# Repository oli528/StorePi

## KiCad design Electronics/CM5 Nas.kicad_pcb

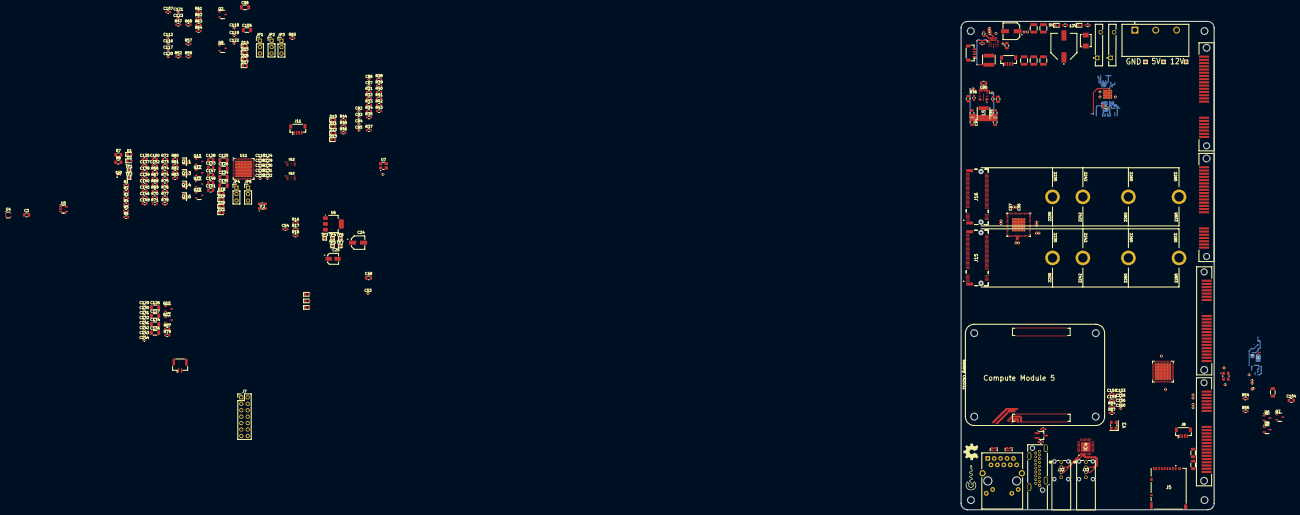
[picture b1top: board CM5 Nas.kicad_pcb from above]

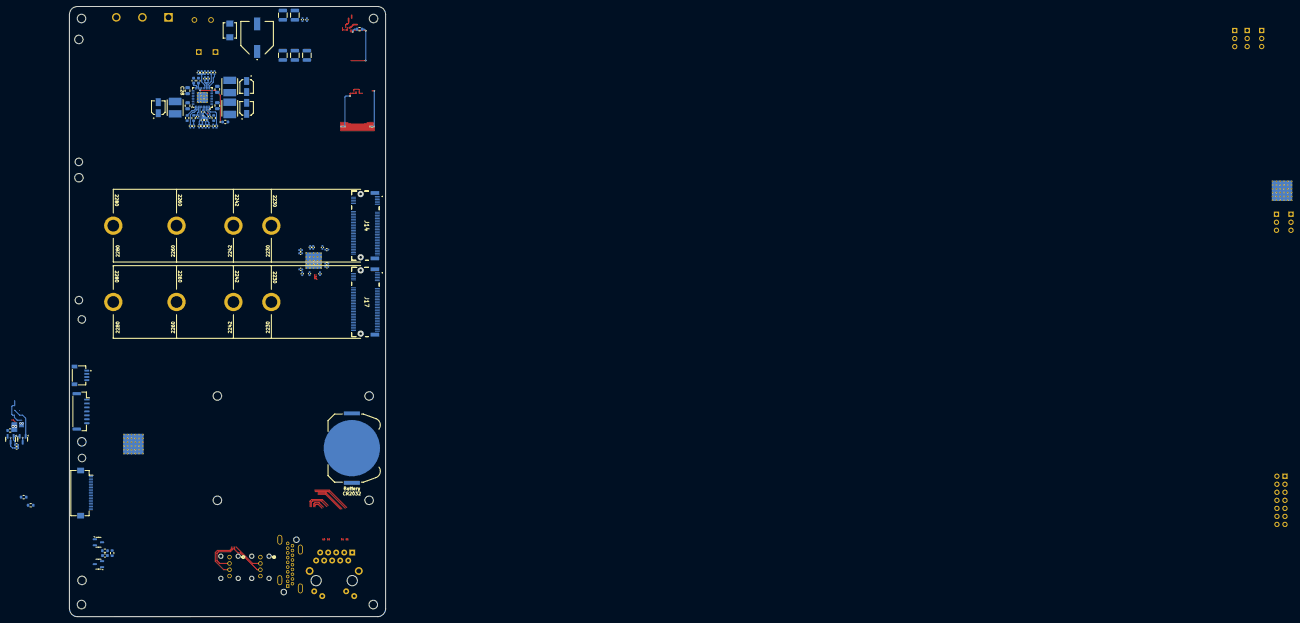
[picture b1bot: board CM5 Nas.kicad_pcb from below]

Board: 4 copper layers, 100.0 x 193.0 mm, 370 parts (78 on the bottom side), 312 nets.

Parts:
+5V1, +12V1: TestPoint; TestPoint_Pad_1.0x1.0mm
BT1: Battery_Cell; BatteryHolder_Keystone_3034_1x20mm
C1, C2, C42, C54, C137, C138, C139, C140, C145, C146, C149, C150, C152, C154, C159: 100n; C_0603_1608Metric
C3, C77, C81: 10u; C_0805_2012Metric
C4, C12: 1u; C_1210_3225Metric
C5, C13: 1000u; EEE0JA152UAP
C6, C7, C8, C9, C14, C15, C16, C17: 10u; C_1210_3225Metric
C10, C11, C18, C19, C44, C56, C57, C58, C59, C60, C61, C62, C63, C64, C65, C66, C67, C68, C69, C70, C71, C72, C73, C74, C75, C76, C79, C82, C83, C84, C85, C86, C87, C88, C89, C109, C110, C111, C112, C116, C117, C120, C121, C123#2: 100n; C_0402_1005Metric
C20, C21, C27, C28: 22u; C_0805_2012Metric
C22, C50, C51: 100p; C_0402_1005Metric
C23: 10u; C_0603_1608Metric
C24: 10u; CAP_EEEFK1H100UR
C25, C32, C34, C37: 22u; CAP_EEEFK1A220AR
C26, C30, C31, C38, C39, C40, C41, C46, C47: 4n7; C_0402_1005Metric
C29: 3u3; C_0603_1608Metric
C33, C35, C36: 47n; C_0402_1005Metric
C43: 100u; CAP_EEEFTH101XAP
C45, C48: 4u7; C_0805_2012Metric
C49, C53: 4u7; C_0402_1005Metric
C52: 2u2; C_0402_1005Metric
C55: 1n; C_0402_1005Metric
C78, C80: 0u47; C_0603_1608Metric
C90, C104, C128, C133, C147, C148, C151: 1u; C_0805_2012Metric
C91, C92, C93, C94: 47u; C_0805_2012Metric
C95, C96, C124, C125, C155, C156: 22p; C_0402_1005Metric
C96#2, C97, C98, C105, C106, C125#2, C126, C126#2, C127, C134, C134#2, C135, C136: 22u; C_1206_3216Metric
C99, C107, C135#2: 1u; C_0603_1608Metric
C100, C101, C102, C103, C108, C113, C114, C115, C119, C120#2, C123, C124#2, C129, C129#2, C130, C130#2, C131, C131#2, C132, C132#2, C141, C142, C143, C144: 10n; C_0402_1005Metric
C118, C119#2, C122: 1u; C_0402_1005Metric
C153, C160: 0u01; C_0402_1005Metric
D1, D3, D6, D7, D8, D9, D10, D11, D12, D13, D14, D15, D16, D17, D18, D19, D20, D21: LED Green; LED_0603_1608Metric
D2: LED Red; LED_0603_1608Metric
D4: D_TVS; SMBJ12A
D5: D_TVS; SMBJ5.0A
F1, F2: Polyfuse; RGEF1200
GND1: TestPoint; TestPoint_Pad_1.0x1.0mm
H1, H2, H3, H4, H5: MountingHole; MountingHole_2.7mm_M2.5
IC1: TPS65251-1RHAR; VQFN-40-1EP_6x6mm_P0.5mm_EP3.5x3.5mm_ThermalVias
IC2: MAX20008AFOC_VY+T; MAX20008AFOCVYT
IC3: LM61480Q3RPHRQ1; LM62460QRPHRQ1
IC4: USB2512B-AEZG; QFN50P600X600X100-37N-D
J1: HDMI_A; AMPHENOL_G45A19071083HR
J2: Conn_01x22_Female; Hirose_FH12-22S-0.5SH_1x22-1MP_P0.50mm_Horizontal
J3: RJ45_RB1-125B8G1A; RJ45_UDE_RB1-125B8G1A
J4: Conn_01x07; JST_GH_SM07B-GHS-TB_1x07-1MP_P1.25mm_Horizontal
J5: Micro_SD_Card_Det; DM3ATSFPEJM5
J6: Conn_01x04; SPARKFUN_PRT-14417
J7: Conn_02x07_Odd_Even; PinHeader_2x07_P2.54mm_Vertical
J8, J9, J11, J12: JST_SHBM04B-SRSS-TB; JST_SH_BM04B-SRSS-TB_1x04-1MP_P1.00mm_Vertical
J10: Conn_01x02; JST_GH_BM02B-GHS-TBT_1x02-1MP_P1.25mm_Vertical
J13: 4DB-P108-03; 4DBP10803
J14, J17: Bus_M.2_Socket_M; 21991195 no holes
J15, J16: Bus_M.2_Socket_M; 21991195
J18, J19, J20, J21: 0877131001; 87713-1001
J22, J23: USB_A; CONN_48204-0001_MOL
JP1, JP2, JP3, JP4, JP5: 3P_JUMPER; PinHeader_1x03_P2.54mm_Vertical
L1, L2, L3: 4u7; INDPM5050X400N
L4: 1u; SRN5040TA1R0M
L5: 2u2; SRN50402R2Y
Module1: ComputeModule5-CM5; Raspberry-Pi-5-Compute-Module
Q1: PMOS; BSS84AKW115
Q2, Q10, Q10#2, Q12, Q15, Q15#2, Q17: NPN; P200_SOT-23
Q2#2: MMBT3904; SOT-23
Q3, Q5, Q6, Q8: AOSS21311C; SOT-23-3
Q4: AOSS21311C; SOT-23
Q7, Q9: MMBT3904; P200_SOT-23
Q11, Q13, Q14, Q16: PMOS; SOT95P237X117-3N
R1, R2, R3, R18, R37, R38, R39, R40, R84: 1K; R_0603_1608Metric
R4, R43, R44, R45, R46: 1k; R_0603_1608Metric
R5, R6, R58, R71, R77: 4K7; R_0603_1608Metric
R7: 0R; R_0805_2012Metric_Pad1.20x1.40mm_HandSolder
R8: nf; R_0805_2012Metric_Pad1.20x1.40mm_HandSolder
R9: 2K2; R_0603_1608Metric
R10: 620; R_0603_1608Metric
R11: 20k; R_0402_1005Metric
R12, R31, R32, R33, R34, R35: 10K; R_0603_1608Metric
R13, R25: 80K6; R_0402_1005Metric
R14: 150k; R_0402_1005Metric
R15, R19, R20: 40K2; R_0402_1005Metric
R16, R17, R61, R62, R63, R64, R80, R81, R82, R83: 270; R_0603_1608Metric
R21: 120k; R_0603_1608Metric
R22: 150k; R_0603_1608Metric
R23: 20K; R_0603_1608Metric
R24: 12K7; R_0402_1005Metric
R26: 383k; R_0402_1005Metric
R27, R28: 20k; R_0603_1608Metric
R29: 22K; C_0402_1005Metric
R30: 12k; R_0603_1608Metric
R36: 10k; R_0402_1005Metric
R41, R42: 12K1; R_0603_1608Metric
R47, R52, R66, R72, R87: 12K; R_0603_1608Metric
R48, R49, R50, R54, R55, R56, R60, R65, R67, R67#2, R68, R69, R70, R73, R74, R74#2, R75, R79: 100K; R_0603_1608Metric
R51: 100K; R_0402_1005Metric
R53: 4K7; R_0402_1005Metric
R57, R76: 10; R_0603_1608Metric
R59, R78: 4K7 1%; R_0603_1608Metric
TP1, TP2, TP3, TP4, TP5, TP6, TP7: TestPoint; TestPoint_Pad_1.0x1.0mm
U1: RT9742SNGV; TSOT-23_HandSoldering
U2, U3: TPD4EUSB30; USON-10_2.5x1.0mm_P0.5mm
U4: 74LVC1G07SE-7; SOT-353_SC-70-5
U5: RT9742GGJ5; SOT-23-5
U6: AMS1117-3.3; SOT-223-3_TabPin2
U7: ASEK-32.768KHZ-L-R-T; Crystal_SMD_3225-4Pin_3.2x2.5mm
U8: ASM1184; QFN-64-1EP_9x9mm_P0.5mm_EP5.2x5.2mm_ThermalVias
U9, U11: JMS561; QFN-64-1EP_8x8mm_P0.4mm_EP6.5x6.5mm_ThermalVias
U10, U12: W25X20CLUXIG_TR; SON50P300X200X60-9N
Y1, Y2, Y3: 30MHz; ABM810000MHZ12D2W

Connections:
+1V2: C58.1, C59.1, C60.1, C61.1, C62.1, C63.1, C69.1, C70.1, C71.1, C72.1, C73.1, C74.1, U8.9 (1V2), U8.15 (1V2), U8.17 (1V2), U8.20 (1V2), U8.26 (1V2), U8.29 (1V2), U8.37 (1V2), U8.43 (1V2), U8.48 (1V2), U8.50 (1V2), U8.61 (1V2), U8.64 (1V2)
+3V3A: C82.1, C83.1, C84.1, C85.1, C86.1, C87.1, R31.1, R32.1, R33.1, R34.1, R35.1, U8.1 (3V_AUX), U8.10 (3V3), U8.21 (3V3), U8.32 (3V3), U8.38 (3V3), U8.56 (3V3)
+5V: R67.1, R74.1
+5V S1: C12.1, C13.1, C14.1, C15.1, C16.1, C17.1, C18.1, C19.1, D5.2 (A2), F2.2
+5V S2: Q5.3 (S), Q8.3 (S), Q13.3 (S), Q16.3 (S), R48.2, R60.1, R67#2.2, R79.2
+5V-HDD0: C96#2.1, C98.2, J18.14 (P7), J18.15 (P8), J18.16 (P9), Q5.1 (D)
+5V-HDD1: C106.2, J19.14 (P7), J19.15 (P8), J19.16 (P9), Q8.1 (D)
+5V-HDD2: C125#2.1, C127.2, J20.14 (P7), J20.15 (P8), J20.16 (P9), Q13.1 (D)
+5V-HDD3: C134.1, C136.2, J21.14 (P7), J21.15 (P8), J21.16 (P9), Q16.1 (D)
+12V: +12V1.1, C4.1, C5.1, C6.1, C7.1, C8.1, C9.1, C10.1, C11.1, C99.1, C104.1, C128.1, C133.1, D4.2 (A2), F1.1, F1.2, J13.3, Q3.3 (S), Q6.3 (S), Q11.3 (S), Q14.3 (S), R9.2, R49.2, R54.2, R68.2, R73.2
+12V-HDD0: C97.1, J18.20 (P13), J18.21 (P14), J18.22 (P15), Q3.1 (D)
+12V-HDD1: C105.1, J19.20 (P13), J19.21 (P14), J19.22 (P15), Q6.1 (D)
+12V-HDD2: C126.1, C126#2.1, J20.20 (P13), J20.21 (P14), J20.22 (P15), Q11.1 (D)
+12V-HDD3: C134#2.1, C135.1, J21.20 (P13), J21.21 (P14), J21.22 (P15), Q14.1 (D)
/Project Architecture/CM5_GPIO/+3V3: D1.2 (A), D2.2 (A), J3.L1, J3.L3, J3.R1 (CT), J4.1, J6.2, Module1.84 (+3.3v_(Output)), Module1.86 (+3.3v_(Output)), R5.1, R6.1, R7.1, U4.5 (VCC), U5.5 (IN)
/Project Architecture/CM5_GPIO/+5V: J11.1, Module1.77 (+5v_(Input)), Module1.79 (+5v_(Input)), Module1.81 (+5v_(Input)), Module1.83 (+5v_(Input)), Module1.85 (+5v_(Input)), Module1.87 (+5v_(Input))
/Project Architecture/CM5_GPIO/+12V: J8.1, J9.1, J12.1
/Project Architecture/CM5_GPIO/CM5 Shut: Module1.54 (GPIO4), Q1.2 (G)
/Project Architecture/CM5_GPIO/EEPROM_nWP: J7.4, Module1.20 (EEPROM_nWP)
/Project Architecture/CM5_GPIO/ETH_LEDG: Module1.17 (Ethernet_nLED2(3.3v)), R1.1
/Project Architecture/CM5_GPIO/ETH_LEDY: Module1.15 (Ethernet_nLED3(3.3v)), R2.1
/Project Architecture/CM5_GPIO/GPIO2: J6.4, Module1.58 (GPIO2), R6.2
/Project Architecture/CM5_GPIO/GPIO3: J6.3, Module1.56 (GPIO3), R5.2
/Project Architecture/CM5_GPIO/GPIO8: J4.5, Module1.39 (GPIO8)
/Project Architecture/CM5_GPIO/GPIO10: J4.3, Module1.44 (GPIO10)
/Project Architecture/CM5_GPIO/GPIO11: J4.4, Module1.38 (GPIO11)
/Project Architecture/CM5_GPIO/GPIO25: J4.6, Module1.41 (GPIO25)
/Project Architecture/CM5_GPIO/GPIO27: J4.7, Module1.48 (GPIO27)
/Project Architecture/CM5_GPIO/GPIO_VREF: Module1.78 (GPIO_VREF(1.8v/3.3v_Input)), R7.2, R8.2
/Project Architecture/CM5_GPIO/PMIC_ENABLE: J7.12, Module1.99 (PMIC_ENABLE)
/Project Architecture/CM5_GPIO/PWM_0: J11.2, Module1.19 (FAN_PWM)
/Project Architecture/CM5_GPIO/PWM_1: J8.2, Module1.31 (GPIO12)
/Project Architecture/CM5_GPIO/PWM_2: J9.2, Module1.28 (GPIO13)
/Project Architecture/CM5_GPIO/PWM_3: J12.2, Module1.55 (GPIO14)
/Project Architecture/CM5_GPIO/PWR_BUT: J7.14, J10.1, Module1.92 (PWR_BUT), Q1.1 (D)
/Project Architecture/CM5_GPIO/SD_CLK: J5.5 (CLK), Module1.57 (SD_CLK)
/Project Architecture/CM5_GPIO/SD_CMD: J5.3 (CMD), Module1.62 (SD_CMD)
/Project Architecture/CM5_GPIO/SD_DAT0: J5.7 (DAT0), Module1.63 (SD_DAT0)
/Project Architecture/CM5_GPIO/SD_DAT1: J5.8 (DAT1), Module1.67 (SD_DAT1)
/Project Architecture/CM5_GPIO/SD_DAT2: J5.1 (DAT2), Module1.69 (SD_DAT2)
/Project Architecture/CM5_GPIO/SD_DAT3: J5.2 (DAT3/CD), Module1.61 (SD_DAT3)
/Project Architecture/CM5_GPIO/SD_PWR: C3.1, J5.4 (VDD), U5.1 (OUT)
/Project Architecture/CM5_GPIO/SD_PWR_ON: Module1.75 (SD_PWR_ON), U5.4 (EN)
/Project Architecture/CM5_GPIO/SYNC_OUT: J7.6, Module1.18 (Ethernet_SYNC_OUT(3.3v))
/Project Architecture/CM5_GPIO/TACHO: J11.4, Module1.16 (FAN_TACHO)
/Project Architecture/CM5_GPIO/TRD0_N: J3.R3 (TD1-), Module1.10 (Ethernet_Pair0_N), U3.4 (D2+), U3.7
/Project Architecture/CM5_GPIO/TRD0_P: J3.R2 (TD1+), Module1.12 (Ethernet_Pair0_P), U3.5 (D2-), U3.6
/Project Architecture/CM5_GPIO/TRD1_N: J3.R5 (TD2-), Module1.6 (Ethernet_Pair1_N), U3.2 (D1-), U3.9
/Project Architecture/CM5_GPIO/TRD1_P: J3.R4 (TD2+), Module1.4 (Ethernet_Pair1_P), U3.1 (D1+), U3.10
/Project Architecture/CM5_GPIO/TRD2_N: J3.R7 (TD3-), Module1.9 (Ethernet_Pair2_N), U2.4 (D2+), U2.7
/Project Architecture/CM5_GPIO/TRD2_P: J3.R6 (TD3+), Module1.11 (Ethernet_Pair2_P), U2.5 (D2-), U2.6
/Project Architecture/CM5_GPIO/TRD3_N: J3.R9 (TD4-), Module1.5 (Ethernet_Pair3_N), U2.2 (D1-), U2.9
/Project Architecture/CM5_GPIO/TRD3_P: J3.R8 (TD4+), Module1.3 (Ethernet_Pair3_P), U2.1 (D1+), U2.10
/Project Architecture/CM5_GPIO/VBAT: BT1.1 (+), Module1.76 (VBAT)
/Project Architecture/CM5_GPIO/nPWR_LED: Module1.95 (LED_nPWR), U4.2
/Project Architecture/CM5_GPIO/nRPIBOOT: J7.2, Module1.93 (nRPIBOOT)
/Project Architecture/CM5_High Speed IO/+5V S1: C1.1, U1.1 (IN)
/Project Architecture/CM5_High Speed IO/DPHY0_C_N: J2.8, Module1.127 (MIPI0_C_N)
/Project Architecture/CM5_High Speed IO/DPHY0_C_P: J2.9, Module1.129 (MIPI0_C_P)
/Project Architecture/CM5_High Speed IO/DPHY0_D0_N: J2.2, Module1.115 (MIPI0_D0_N)
/Project Architecture/CM5_High Speed IO/DPHY0_D0_P: J2.3, Module1.117 (MIPI0_D0_P)
/Project Architecture/CM5_High Speed IO/DPHY0_D1_N: J2.5, Module1.121 (MIPI0_D1_N)
/Project Architecture/CM5_High Speed IO/DPHY0_D1_P: J2.6, Module1.123 (MIPI0_D1_P)
/Project Architecture/CM5_High Speed IO/DPHY0_D2_N: J2.11, Module1.133 (MIPI0_D2_N)
/Project Architecture/CM5_High Speed IO/DPHY0_D2_P: J2.12, Module1.135 (MIPI0_D2_P)
/Project Architecture/CM5_High Speed IO/DPHY0_D3_N: J2.14, Module1.139 (MIPI0_D3_N)
/Project Architecture/CM5_High Speed IO/DPHY0_D3_P: J2.15, Module1.141 (MIPI0_D3_P)
/Project Architecture/CM5_High Speed IO/HDMI0_CEC: J1.13 (CEC), Module1.151 (HDMI0_CEC)
/Project Architecture/CM5_High Speed IO/HDMI0_CK_N: J1.12 (CK-), Module1.190 (HDMI0_CLK_N)
/Project Architecture/CM5_High Speed IO/HDMI0_CK_P: J1.10 (CK+), Module1.188 (HDMI0_CLK_P)
/Project Architecture/CM5_High Speed IO/HDMI0_D0_N: J1.9 (D0-), Module1.184 (HDMI0_TX0_N)
/Project Architecture/CM5_High Speed IO/HDMI0_D0_P: J1.7 (D0+), Module1.182 (HDMI0_TX0_P)
/Project Architecture/CM5_High Speed IO/HDMI0_D1_N: J1.6 (D1-), Module1.178 (HDMI0_TX1_N)
/Project Architecture/CM5_High Speed IO/HDMI0_D1_P: J1.4 (D1+), Module1.176 (HDMI0_TX1_P)
/Project Architecture/CM5_High Speed IO/HDMI0_D2_N: J1.3 (D2-), Module1.172 (HDMI0_TX2_N)
/Project Architecture/CM5_High Speed IO/HDMI0_D2_P: J1.1 (D2+), Module1.170 (HDMI0_TX2_P)
/Project Architecture/CM5_High Speed IO/HDMI0_HOTPLUG: J1.19 (HPD), Module1.153 (HDMI0_HOTPLUG)
/Project Architecture/CM5_High Speed IO/HDMI0_SCL: J1.15 (SCL), Module1.200 (HDMI0_SCL)
/Project Architecture/CM5_High Speed IO/HDMI0_SDA: J1.16 (SDA), Module1.199 (HDMI0_SDA)
/Project Architecture/CM5_High Speed IO/HDMI_5v: C2.1, J1.18 (+5V), U1.2 (OUT)
/Project Architecture/Input/+5V: +5V1.1, F2.1, J13.2
/Project Architecture/M.2 Drives/+3V3 M.2: C64.1, C91.1, C92.1, C93.1, C94.1, D10.2 (A), D11.2 (A), D12.2 (A), D13.2 (A), IC3.5 (BIAS), IC3.7 (FB), J14.2 (3.3V), J14.4 (3.3V), J14.70 (3.3V), J14.72 (3.3V), J14.74 (3.3V), J15.2 (3.3V), J15.4 (3.3V), J15.70 (3.3V), J15.72 (3.3V), J15.74 (3.3V), J16.2 (3.3V), J16.4 (3.3V), J16.70 (3.3V), J16.72 (3.3V), J16.74 (3.3V), J17.2 (3.3V), J17.4 (3.3V), J17.70 (3.3V), J17.72 (3.3V), J17.74 (3.3V), L5.2, R36.2, U7.1 (EN), U7.4 (VDD)
/Project Architecture/M.2 Drives/+5V S1: C77.2, C78.2, C80.1, C81.1, IC3.2 (VIN2), IC3.13 (EN), IC3.14 (VIN1)
/Project Architecture/M.2 Drives/BOOT: C79.1, IC3.16 (SW), L5.1
/Project Architecture/M.2 Drives/PCIE_nCLKREQ: J14.52 (~CLKREQ), J15.52 (~CLKREQ), J16.52 (~CLKREQ), J17.52 (~CLKREQ)
/Project Architecture/M.2 Drives/PCIE_nWAKE: J14.54 (~PEWAKE), J15.54 (~PEWAKE), J16.54 (~PEWAKE), J17.54 (~PEWAKE)
/Project Architecture/M.2 Drives/PCIe_CLK_N_1: J16.53 (REFCLKn), U8.19 (REFCLKN_1)
/Project Architecture/M.2 Drives/PCIe_CLK_N_2: J17.53 (REFCLKn), U8.28 (REFCLKN_2)
/Project Architecture/M.2 Drives/PCIe_CLK_N_3: J15.53 (REFCLKn), U8.45 (REFCLKN_3)
/Project Architecture/M.2 Drives/PCIe_CLK_N_4: J14.53 (REFCLKn), U8.63 (REFCLKN_4)
/Project Architecture/M.2 Drives/PCIe_CLK_P_1: J16.55 (REFCLKp), U8.18 (REFCLKP_1)
/Project Architecture/M.2 Drives/PCIe_CLK_P_2: J17.55 (REFCLKp), U8.27 (REFCLKP_2)
/Project Architecture/M.2 Drives/PCIe_CLK_P_3: J15.55 (REFCLKp), U8.44 (REFCLKP_3)
/Project Architecture/M.2 Drives/PCIe_CLK_P_4: J14.55 (REFCLKp), U8.62 (REFCLKP_4)
/Project Architecture/M.2 Drives/PCIe_RX_N_1: J16.41 (PETn0), U8.14 (RXN_1)
/Project Architecture/M.2 Drives/PCIe_RX_N_2: J17.41 (PETn0), U8.25 (RXN_2)
/Project Architecture/M.2 Drives/PCIe_RX_N_3: J15.41 (PETn0), U8.42 (RXN_3)
/Project Architecture/M.2 Drives/PCIe_RX_N_4: J14.41 (PETn0), U8.60 (RXN_4)
/Project Architecture/M.2 Drives/PCIe_RX_P_1: J16.43 (PETp0), U8.13 (RXP_1)
/Project Architecture/M.2 Drives/PCIe_RX_P_2: J17.43 (PETp0), U8.24 (RXP_2)
/Project Architecture/M.2 Drives/PCIe_RX_P_3: J15.43 (PETp0), U8.41 (RXP_3)
/Project Architecture/M.2 Drives/PCIe_RX_P_4: J14.43 (PETp0), U8.59 (RXP_4)
/Project Architecture/M.2 Drives/PCIe_TX_N_1: C57.1, J16.47 (PERn0)
/Project Architecture/M.2 Drives/PCIe_TX_N_2: C66.1, J17.47 (PERn0)
/Project Architecture/M.2 Drives/PCIe_TX_N_3: C68.1, J15.47 (PERn0)
/Project Architecture/M.2 Drives/PCIe_TX_N_4: C76.1, J14.47 (PERn0)
/Project Architecture/M.2 Drives/PCIe_TX_P_1: C56.1, J16.49 (PERp0)
/Project Architecture/M.2 Drives/PCIe_TX_P_2: C65.1, J17.49 (PERp0)
/Project Architecture/M.2 Drives/PCIe_TX_P_3: C67.1, J15.49 (PERp0)
/Project Architecture/M.2 Drives/PCIe_TX_P_4: C75.1, J14.49 (PERp0)
/Project Architecture/M.2 Drives/PERST: J14.50 (~PERST), J15.50 (~PERST), J16.50 (~PERST), J17.50 (~PERST), U8.2 (RES_OUT)
/Project Architecture/M.2 Drives/RS1: IC3.10 (~RESET_1), IC3.19 (~RESET_2), R36.1
/Project Architecture/M.2 Drives/SUSCLK: J14.68 (SUSCLK), J15.68 (SUSCLK), J16.68 (SUSCLK), J17.68 (SUSCLK), U7.3 (Out)
/Project Architecture/M.2 Drives/TX_N_3: C68.2, U8.40 (TXN_3)
/Project Architecture/M.2 Drives/TX_P_3: C67.2, U8.39 (TXP_3)
/Project Architecture/M.2 Drives/VCC: C90.1, IC3.6 (VCC_1), IC3.9 (RT), IC3.11 (SPSP), IC3.18 (VCC_2)
/Project Architecture/Power/+1V2: C37.1, C39.1, L3.2, R12.1, R20.1, TP6.1
/Project Architecture/Power/+1V2A: C31.1, C32.1, L1.2, R15.1, TP4.1
/Project Architecture/Power/+3V3: C25.1, R16.2, TP3.1, U6.2 (VO)
/Project Architecture/Power/+3V3A: C34.1, C38.1, L2.2, R17.2, R19.1, TP5.1
/Project Architecture/Power/+5V S1: C20.2, C21.2, C24.1, C27.2, C28.1, IC1.11 (EN1), IC1.13 (VIN1), IC1.18 (VIN2), IC1.20 (EN2), IC1.32 (VIN_1), IC1.33 (VIN_2), IC1.34 (VIN_3), IC1.38 (VIN3), IC1.40 (EN3), U6.3 (VI)
/Project Architecture/Power/+5V S2: C48.1, IC2.1 (OUT), L4.2, R18.2, R23.1, TP7.1
/Project Architecture/Power/FB1: C39.2, IC1.7 (FB1), R20.2, R25.1
/Project Architecture/Power/FB2: C31.2, IC1.24 (FB2), R13.1, R15.2
/Project Architecture/Power/FB3: C38.2, IC1.4 (FB3), R19.2, R24.1
/Project Architecture/Power/SUP: C43.1, C44.1, C45.1, C53.1, C54.1, IC2.9 (SUPSW), IC2.10 (SUP), IC2.11 (EN)
/Project Architecture/Sata Drives 1/1V2A: C119#2.1, C120.1, C121.1, C122.1, C123#2.1, U9.29 (UA-VCCK), U9.37 (SA-VCCK), U9.40 (SA-VCCK), U9.46 (SA-VCCK)
/Project Architecture/Sata Drives 1/1V2D: C116.1, C117.1, C118.1, U9.4 (VCCK), U9.12 (VCCK), U9.17 (VCCK), U9.20 (VCCK), U9.32 (UA-VCCK), U9.51 (VCCK), U9.57 (VCCK)
/Project Architecture/Sata Drives 1/3V3: C109.1, C110.1, JP1.1 (A), JP2.1 (A), R59.1, R65.2, U9.10 (VCCO), U9.52 (VCCO), U10.8 (VCC)
/Project Architecture/Sata Drives 1/3V3A: C111.1, C112.1, U9.26 (UA-VCCH), U9.33 (XA-VCCH), U9.43 (SA-VCCH)
/Project Architecture/Sata Drives 1/GPIO1: R59.2, U9.1 (GPIO1/RX)
/Project Architecture/Sata Drives 1/GPIO2: U9.18 (GPIO2/PSSO), U10.1 (~CS)
/Project Architecture/Sata Drives 1/GPIO5: JP1.2 (C), U9.6 (GPIO5/MISO)
/Project Architecture/Sata Drives 1/GPIO7: JP2.2 (C), U9.5 (GPIO7/SSI)
/Project Architecture/Sata Drives 1/GPIO8: R56.2, R58.1, U9.8 (GPIO8/D1_PWR)
/Project Architecture/Sata Drives 1/GPIO9: R51.2, R53.1, U9.50 (GPIO9/D0_PWR)
/Project Architecture/Sata Drives 1/GPIO10: R62.1, U9.53 (GPIO10/LED2)
/Project Architecture/Sata Drives 1/GPIO11: R61.1, U9.55 (GPIO11/LED0)
/Project Architecture/Sata Drives 1/GPIO12: R63.1, U9.11 (GPIO12/LED1)
/Project Architecture/Sata Drives 1/GPIO13: U9.15 (GPIO13/PMOSI), U10.5 (DI(IO0))
/Project Architecture/Sata Drives 1/GPIO14: R64.1, U9.9 (GPIO14/LED3)
/Project Architecture/Sata Drives 1/GPIO15: U9.13 (GPIO15/PSCK), U10.6 (CLK)
/Project Architecture/Sata Drives 1/GPIO16: U9.14 (GPIO16/PMISO), U10.2 (DO(IO1))
/Project Architecture/Sata Drives 1/HDD0_DET: Q2.1 (C), Q2#2.1 (C), Q4.2 (B), R51.1
/Project Architecture/Sata Drives 1/HDD1_DET: Q7.2 (B), Q9.1 (C), R56.1
/Project Architecture/Sata Drives 1/S0_RXN: C103.1, U9.39 (S0-RXN)
/Project Architecture/Sata Drives 1/S0_RXP: C102.1, U9.38 (S0-RXP)
/Project Architecture/Sata Drives 1/S0_TXN: C100.1, U9.41 (S0-TXN)
/Project Architecture/Sata Drives 1/S0_TXP: C101.1, U9.42 (S0-TXP)
/Project Architecture/Sata Drives 1/S1_RXN: C115.1, U9.45 (S1-RXN)
/Project Architecture/Sata Drives 1/S1_RXP: C114.1, U9.44 (S1-RXP)
/Project Architecture/Sata Drives 1/S1_TXN: C108.1, U9.47 (S1-TXN)
/Project Architecture/Sata Drives 1/S1_TXP: C113.1, U9.48 (S1-TXP)
/Project Architecture/Sata Drives 1/S-REXT: R47.1, U9.36 (S-REXT)
/Project Architecture/Sata Drives 1/U-REXT: R52.2, U9.25 (UREXT)
/Project Architecture/Sata Drives 1/VBUS-S: C107.1, R57.1, U9.16 (VBUS_SENSE)
/Project Architecture/Sata Drives 1/XIN: C95.1, U9.35 (XI), Y1.1
/Project Architecture/Sata Drives 1/XOUT: C96.1, U9.34 (XO), Y1.3
/Project Architecture/Sata Drives 2/1V2A: C148.1, C149.1, C150.1, C151.1, C152.1, U11.29 (UA-VCCK), U11.37 (SA-VCCK), U11.40 (SA-VCCK), U11.46 (SA-VCCK)
/Project Architecture/Sata Drives 2/1V2D: C145.1, C146.1, C147.1, U11.4 (VCCK), U11.12 (VCCK), U11.17 (VCCK), U11.20 (VCCK), U11.32 (UA-VCCK), U11.51 (VCCK), U11.57 (VCCK)
/Project Architecture/Sata Drives 2/3V3: C137.1, C138.1, JP4.1 (A), JP5.1 (A), R78.1, U11.10 (VCCO), U11.52 (VCCO), U12.8 (VCC)
/Project Architecture/Sata Drives 2/3V3A: C139.1, C140.1, U11.26 (UA-VCCH), U11.33 (XA-VCCH), U11.43 (SA-VCCH)
/Project Architecture/Sata Drives 2/GPIO1: R78.2, U11.1 (GPIO1/RX)
/Project Architecture/Sata Drives 2/GPIO2: U11.18 (GPIO2/PSSO), U12.1 (~CS)
/Project Architecture/Sata Drives 2/GPIO5: JP4.2 (C), U11.6 (GPIO5/MISO)
/Project Architecture/Sata Drives 2/GPIO7: JP5.2 (C), U11.5 (GPIO7/SSI)
/Project Architecture/Sata Drives 2/GPIO8: R75.2, R77.1, U11.8 (GPIO8/D1_PWR)
/Project Architecture/Sata Drives 2/GPIO9: R70.2, R71.1, U11.50 (GPIO9/D0_PWR)
/Project Architecture/Sata Drives 2/GPIO10: R81.1, U11.53 (GPIO10/LED2)
/Project Architecture/Sata Drives 2/GPIO11: R80.1, U11.55 (GPIO11/LED0)
/Project Architecture/Sata Drives 2/GPIO12: R82.1, U11.11 (GPIO12/LED1)
/Project Architecture/Sata Drives 2/GPIO13: U11.15 (GPIO13/PMOSI), U12.5 (DI(IO0))
/Project Architecture/Sata Drives 2/GPIO14: R83.1, U11.9 (GPIO14/LED3)
/Project Architecture/Sata Drives 2/GPIO15: U11.13 (GPIO15/PSCK), U12.6 (CLK)
/Project Architecture/Sata Drives 2/GPIO16: U11.14 (GPIO16/PMISO), U12.2 (DO(IO1))
/Project Architecture/Sata Drives 2/HDD2_DET: Q10.1 (C), Q10#2.1 (C), Q12.2 (B), R70.1
/Project Architecture/Sata Drives 2/HDD3_DET: Q15.1 (C), Q15#2.2 (B), Q17.1 (C), R75.1
/Project Architecture/Sata Drives 2/S2_RXN: C124#2.1, C132.1, U11.39 (S0-RXN)
/Project Architecture/Sata Drives 2/S2_RXP: C123.1, C131.1, U11.38 (S0-RXP)
/Project Architecture/Sata Drives 2/S2_TXN: C119.1, C129#2.1, U11.41 (S0-TXN)
/Project Architecture/Sata Drives 2/S2_TXP: C120#2.1, C130.1, C130#2.1, C142.1, U11.42 (S0-TXP)
/Project Architecture/Sata Drives 2/S3_RXN: C132#2.1, C144.1, U11.45 (S1-RXN)
/Project Architecture/Sata Drives 2/S3_RXP: C131#2.1, C143.1, U11.44 (S1-RXP)
/Project Architecture/Sata Drives 2/S3_TXN: C129.1, C141.1, U11.47 (S1-TXN)
/Project Architecture/Sata Drives 2/S-REXT: R66.1, U11.36 (S-REXT)
/Project Architecture/Sata Drives 2/U-REXT: R72.2, U11.25 (UREXT)
/Project Architecture/Sata Drives 2/VBUS-S: C135#2.1, R76.1, U11.16 (VBUS_SENSE)
/Project Architecture/Sata Drives 2/XIN: C124.1, U11.35 (XI), Y2.1
/Project Architecture/Sata Drives 2/XOUT: C125.1, U11.34 (XO), Y2.3
/Project Architecture/Usb Switch/+3V3: IC4.15 (VDD33_1), IC4.23 (VDD33_2), IC4.26 (RESET_N), R84.1
/Project Architecture/Usb Switch/+3V3A: IC4.5 (VDDA33_1), IC4.10 (VDDA33_2), IC4.29 (VDDA33_3), IC4.36 (VDDA33_4)
/Project Architecture/Usb Switch/+5V S1: J22.1 (VBUS), J23.1 (VBUS)
/Project Architecture/Usb Switch/D1+: IC4.2 (USBDP_DN1/PRT_DIS_P1), J22.3 (D+)
/Project Architecture/Usb Switch/D1-: IC4.1 (USBDM_DN1/PRT_DIS_M1), J22.2 (D-)
/Project Architecture/Usb Switch/D2+: IC4.4 (USBDP_DN2/PRT_DIS_P2), J23.3 (D+)
/Project Architecture/Usb Switch/D2-: IC4.3 (USBDM_DN2/PRT_DIS_M2), J23.2 (D-)
/Project Architecture/Usb Switch/XIN: C155.1, IC4.33 (XTALIN/CLKIN), Y3.1
/Project Architecture/Usb Switch/XOUT: C156.1, IC4.32 (XTALOUT), Y3.3
unnamed: C26.1, R11.2
unnamed: C46.1, R27.2
unnamed: C47.1, R28.2
unnamed: C55.1, R29.2
unnamed: D1.1 (K), R3.1, TP1.1
unnamed: D2.1 (K), R4.1, TP2.1
unnamed: D3.2 (A), R9.1
unnamed: D6.2 (A), R10.1
unnamed: D7.2 (A), R16.1
unnamed: D8.2 (A), R17.1
unnamed: D9.2 (A), R18.1
unnamed: D10.1 (K), R46.1
unnamed: D11.1 (K), R43.1
unnamed: D12.1 (K), R44.1
unnamed: D13.1 (K), R45.1
unnamed: D14.2 (A), R61.2
unnamed: D15.2 (A), R62.2
unnamed: D16.2 (A), R63.2
unnamed: D17.2 (A), R64.2
unnamed: D18.2 (A), R80.2
unnamed: D19.2 (A), R81.2
unnamed: D20.2 (A), R82.2
unnamed: D21.2 (A), R83.2
unnamed: C36.1, IC1.12 (BST1)
unnamed: C33.2, IC1.19 (BST2)
unnamed: C35.1, IC1.39 (BST3)
unnamed: C51.1, IC1.8 (CMP1), R28.1
unnamed: C50.1, IC1.3 (CMP3), R27.1
unnamed: C22.1, IC1.23 (COMP2), R11.1
unnamed: C36.2, IC1.14 (LX1_1), IC1.15 (LX1_2), L3.1
unnamed: C33.1, IC1.16 (LX2_1), IC1.17 (LX2_2), L1.1
unnamed: C35.2, IC1.36 (LX3_1), IC1.37 (LX3_2), L2.1
unnamed: IC1.27 (PGOOD), R12.2
unnamed: IC1.10 (RLIM1), R22.1
unnamed: IC1.21 (RLIM2), R14.1
unnamed: IC1.1 (RLIM3), R21.1
unnamed: IC1.6 (ROSC), R26.2
unnamed: C41.1, IC1.9 (SS1)
unnamed: C30.1, IC1.22 (SS2)
unnamed: C40.1, IC1.2 (SS3)
unnamed: C29.2, IC1.29 (V3V)
unnamed: C23.2, IC1.28 (V7V)
unnamed: C52.2, IC2.13 (BIAS), IC2.16 (FB)
unnamed: C42.1, IC2.3 (BST)
unnamed: C49.1, IC2.15 (COMP), R29.1
unnamed: IC2.17 (FOSC), R30.1
unnamed: C42.2, IC2.6 (LX), L4.1
unnamed: IC2.2 (~RESET), R23.2
unnamed: C79.2, IC3.3 (RBOOT), IC3.4 (CBOOT)
unnamed: C153.1, C154.1, IC4.14 (CRFILT)
unnamed: C159.1, C160.1, IC4.34 (PLLFILT)
unnamed: IC4.35 (RBIAS), R87.2
unnamed: IC4.27 (VBUS_DET), R84.2
unnamed: J3.L2, R1.2
unnamed: J3.L4, R2.2
unnamed: J14.10 (DAS/~DSS/~LED1), R43.2
unnamed: J15.10 (DAS/~DSS/~LED1), R44.2
unnamed: J16.10 (DAS/~DSS/~LED1), R45.2
unnamed: J17.10 (DAS/~DSS/~LED1), R46.2
unnamed: J18.12 (P5), Q2#2.2 (B), R48.1
unnamed: C103.2, J18.2 (S2)
unnamed: C102.2, J18.3 (S3)
unnamed: C101.2, J18.5 (S5)
unnamed: C100.2, J18.6 (S6)
unnamed: J19.12 (P5), Q9.2 (B), R60.2
unnamed: C115.2, J19.2 (S2)
unnamed: C114.2, J19.3 (S3)
unnamed: C113.2, J19.5 (S5)
unnamed: C108.2, J19.6 (S6)
unnamed: J20.12 (P5), Q10#2.2 (B), R67#2.1
unnamed: C132.2, J20.2 (S2)
unnamed: C131.2, J20.3 (S3)
unnamed: C130#2.2, J20.5 (S5)
unnamed: C129#2.2, J20.6 (S6)
unnamed: J21.12 (P5), Q17.2 (B), R79.1
unnamed: C144.2, J21.2 (S2)
unnamed: C143.2, J21.3 (S3)
unnamed: C142.2, J21.5 (S5)
unnamed: C141.2, J21.6 (S6)
unnamed: JP3.1 (A), R65.1, U10.3 (~WP)
unnamed: Module1.21 (LED_nACT), R3.2
unnamed: C99.2, Q3.2 (G), Q5.2 (G), R50.2
unnamed: Q4.1 (C), R49.1, R50.1
unnamed: C104.2, Q6.2 (G), Q8.2 (G), R55.2
unnamed: Q7.1 (C), R54.1, R55.1
unnamed: Q10.2 (B), R67.2
unnamed: C128.2, Q11.2 (G), Q13.2 (G), R69.2
unnamed: Q12.1 (C), R68.1, R69.1
unnamed: C133.2, Q14.2 (G), Q16.2 (G), R74#2.2
unnamed: Q15.2 (B), R74.2
unnamed: Q15#2.1 (C), R73.1, R74#2.1
unnamed: R4.2, U4.4
unnamed: U2.3 (GND), U2.8 (GND)
unnamed: U3.3 (GND), U3.8 (GND)
unnamed: R35.2, U8.4 (GPIO_0)
unnamed: R31.2, U8.31 (GPIO_1)
unnamed: R38.1, U8.5 (GPIO_2)
unnamed: R34.2, U8.34 (GPIO_3)
unnamed: R37.1, U8.8 (GPIO_4)
unnamed: R32.2, U8.30 (GPIO_5)
unnamed: R39.1, U8.35 (GPIO_6)
unnamed: R33.2, U8.36 (GPIO_7)
unnamed: R41.1, U8.16 (REXT1)
unnamed: R42.1, U8.49 (REXT2)
unnamed: R40.1, U8.33 (TEST_EN)
unnamed: C57.2, U8.12 (TXN_1)
unnamed: C66.2, U8.23 (TXN_2)
unnamed: C76.2, U8.58 (TXN_4)
unnamed: C89.2, U8.55 (TXN_IN)
unnamed: C56.2, U8.11 (TXP_1)
unnamed: C65.2, U8.22 (TXP_2)
unnamed: C75.2, U8.57 (TXP_4)
unnamed: C88.2, U8.54 (TXP_IN)
gnd: BT1.2 (-), C1.2, C2.2, C3.2, C4.2, C5.2, C6.2, C7.2, C8.2, C9.2, C10.2, C11.2, C12.2, C13.2, C14.2, C15.2, C16.2, C17.2, C18.2, C19.2, C20.1, C21.1, C22.2, C23.1, C24.2, C25.2, C26.2, C27.1, C28.2, C29.1, C30.2, C32.2, C34.2, C37.2, C40.2, C41.2, C43.2, C44.2, C45.2, C46.2, C47.2, C48.2, C49.2, C50.2, C51.2, C52.1, C53.2, C54.2, C55.2, C58.2, C59.2, C60.2, C61.2, C62.2, C63.2, C64.2, C69.2, C70.2, C71.2, C72.2, C73.2, C74.2, C77.1, C78.1, C80.2, C81.2, C82.2, C83.2, C84.2, C85.2, C86.2, C87.2, C90.2, C91.2, C92.2, C93.2, C94.2, C95.2, C96.2, C96#2.2, C97.2, C98.1, C105.2, C106.1, C107.2, C109.2, C110.2, C111.2, C112.2, C116.2, C117.2, C118.2, C119#2.2, C120.2, C121.2, C122.2, C123#2.2, C124.2, C125.2, C125#2.2, C126.2, C126#2.2, C127.1, C134.2, C134#2.2, C135.2, C135#2.2, C136.1, C137.2, C138.2, C139.2, C140.2, C145.2, C146.2, C147.2, C148.2, C149.2, C150.2, C151.2, C152.2, C153.2, C154.2, C155.2, C156.2, C159.2, C160.2, D3.1 (K), D4.1 (A1), D5.1 (A1), D6.1 (K), D7.1 (K), D8.1 (K), D9.1 (K), D14.1 (K), D15.1 (K), D16.1 (K), D17.1 (K), D18.1 (K), D19.1 (K), D20.1 (K), D21.1 (K), GND1.1, IC1.25 (LOW_P), IC1.26 (GND_1), IC1.30 (AGND), IC1.31 (GND_2), IC1.35 (GND_3), IC1.41 (EP), IC2.4 (PGND_1), IC2.5 (PGND_2), IC2.7 (PGND_3), IC2.8 (PGND_4), IC2.12 (SYNC), IC2.14 (GND), IC3.1 (PGND2_1), IC3.8 (AGND), IC3.12 (SYNC/_MODE), IC3.15 (PGND1_1), IC3.17 (PGND2_2), IC3.20 (PGND1_2), IC4.37 (GROUND_PAD_(VSS)), J1.2 (D2S), J1.5 (D1S), J1.8 (D0S), J1.11 (CKS), J1.17 (GND), J2.1, J2.4, J2.7, J2.10, J2.13, J2.16, J2.19, J3.R10 (GND), J3.SH, J4.2, J5.6 (VSS), J6.1, J7.1, J7.3, J7.5, J7.7, J7.9, J7.11, J7.13, J8.3, J9.3, J10.2, J11.3, J12.3, J13.1, J14.1 (GND), J14.3 (GND), J14.9 (GND), J14.21 (GND), J14.27 (GND), J14.33 (GND), J14.39 (GND), J14.45 (GND), J14.51 (GND), J14.57 (GND), J14.71 (GND), J14.73 (GND), J14.75 (GND), J15.1 (GND), J15.3 (GND), J15.9 (GND), J15.21 (GND), J15.27 (GND), J15.33 (GND), J15.39 (GND), J15.45 (GND), J15.51 (GND), J15.57 (GND), J15.71 (GND), J15.73 (GND), J15.75 (GND), J15.M1 (GND2230), J15.M2 (GND2242), J15.M3 (GND2260), J15.M4 (GND2280), J16.1 (GND), J16.3 (GND), J16.9 (GND), J16.21 (GND), J16.27 (GND), J16.33 (GND), J16.39 (GND), J16.45 (GND), J16.51 (GND), J16.57 (GND), J16.71 (GND), J16.73 (GND), J16.75 (GND), J16.M1 (GND2230), J16.M2 (GND2242), J16.M3 (GND2260), J16.M4 (GND2280), J17.1 (GND), J17.3 (GND), J17.9 (GND), J17.21 (GND), J17.27 (GND), J17.33 (GND), J17.39 (GND), J17.45 (GND), J17.51 (GND), J17.57 (GND), J17.71 (GND), J17.73 (GND), J17.75 (GND), J18.1 (S1), J18.4 (S4), J18.7 (S7), J18.11 (P4), J18.13 (P6), J18.17 (P10), J18.18 (P11), J18.19 (P12), J19.1 (S1), J19.4 (S4), J19.7 (S7), J19.11 (P4), J19.13 (P6), J19.17 (P10), J19.18 (P11), J19.19 (P12), J20.1 (S1), J20.4 (S4), J20.7 (S7), J20.11 (P4), J20.13 (P6), J20.17 (P10), J20.18 (P11), J20.19 (P12), J21.1 (S1), J21.4 (S4), J21.7 (S7), J21.11 (P4), J21.13 (P6), J21.17 (P10), J21.18 (P11), J21.19 (P12), J22.4 (GND), J23.4 (GND), JP1.3 (B), JP2.3 (B), JP3.2 (C), JP4.3 (B), JP5.3 (B), Module1.1 (GND), Module1.2 (GND), Module1.7 (GND), Module1.8 (GND), Module1.13 (GND), Module1.14 (GND), Module1.22 (GND), Module1.23 (GND), Module1.32 (GND), Module1.33 (GND), Module1.42 (GND), Module1.43 (GND), Module1.52 (GND), Module1.53 (GND), Module1.59 (GND), Module1.60 (GND), Module1.65 (GND), Module1.66 (GND), Module1.71 (GND), Module1.74 (GND), Module1.98 (GND), Module1.107 (GND), Module1.108 (GND), Module1.113 (GND), Module1.114 (GND), Module1.119 (GND), Module1.120 (GND), Module1.125 (GND), Module1.126 (GND), Module1.131 (GND), Module1.132 (GND), Module1.137 (GND), Module1.138 (GND), Module1.144 (GND), Module1.150 (GND), Module1.155 (GND), Module1.156 (GND), Module1.161 (GND), Module1.162 (GND), Module1.167 (GND), Module1.168 (GND), Module1.173 (GND), Module1.174 (GND), Module1.179 (GND), Module1.180 (GND), Module1.185 (GND), Module1.186 (GND), Module1.191 (GND), Module1.192 (GND), Module1.197 (GND), Module1.198 (GND), Q1.3 (S), Q2.3 (E), Q2#2.3 (E), Q4.3 (E), Q7.3 (E), Q9.3 (E), Q10.3 (E), Q10#2.3 (E), Q12.3 (E), Q15.3 (E), Q15#2.3 (E), Q17.3 (E), R10.2, R13.2, R14.2, R21.2, R22.2, R24.2, R25.2, R26.1, R30.2, R37.2, R38.2, R39.2, R40.2, R41.2, R42.2, R47.2, R52.1, R53.2, R58.2, R66.2, R71.2, R72.1, R77.2, R87.1, U1.3 (GND), U4.3 (GND), U5.2 (GND), U6.1 (GND), U7.2 (GND), U8.53 (GND), U8.65 (GND), U9.56 (TESTn), U9.58 (GND), U9.59 (GND), U9.65 (ePAD), U10.4 (GND), U10.9 (EXP), U11.56 (TESTn), U11.58 (GND), U11.59 (GND), U11.65 (ePAD), U12.3 (~WP), U12.4 (GND), U12.9 (EXP), Y1.2, Y1.4, Y2.2, Y2.4, Y3.2, Y3.4

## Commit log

2025-06-10 Initial Comment
    No design
2025-06-10 Progress on Block Diagram
2025-06-10 PSU added
2025-06-11 CM5 IO done
2025-06-11 Progress in power input and sata power option
2025-06-12 Libaries added
2025-06-12 Your commit message
2025-06-17 Voltage calcs
2025-06-18 Digital Reg with multiple v
2025-06-18 Digital Reg Changed
2025-06-19 Footprints added
2025-06-19 block diagram updated
2025-06-19 Drives moved
2025-06-21 Sheet name edit and changed to net labels
2025-06-23 Notation changed on M.2 Sheet
2025-06-25 Started Ethernet design
2025-06-26 Buck converter output voltage changed
2025-06-29 etherenet schematic
2025-06-29 switched from KSZ9893RNX to SJA1105PEL for sgmii support
2025-07-02 Swiitched to JSM561
2025-07-03 Removed Ethernet
2025-07-03 Sheets neatened
2025-07-04 More Fans
2025-07-05 Create LICENSE
2025-07-05 RP2040 Added, Files Structure Changed
2025-07-05 back up moved
2025-07-05 Rp2040 Power Sequence finished and general cleaning
2025-07-06 Starting the Sheet connections
2025-07-08 Footprints Selected
2025-07-13 Footprints selected, Hiracicle connections created, Pcb next
2025-07-14 Sata Port Changed
2025-07-16 Changed sata port
2025-07-16 More pcbing
2025-08-04 More pcb arangment, verticle ports
2025-08-05 Power symbols changed and sata hub fixed schem
2025-08-07 Fans
2025-08-07 stuff
